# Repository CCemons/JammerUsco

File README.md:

# JammerUsco — Prototipo Inhibidor de Señales en la Banda Libre de 2.4 GHz

**Universidad Surcolombiana (USCO)** — Facultad de Ingeniería — Programa de Ingeniería Electrónica  
**Autores:** Camilo Andrés Castañeda Polo ([@CCemons](https://github.com/CCemons)) · Daniel Camilo Torres Quintana ([@BlackSorix](https://github.com/BlackSorix))  
**Director:** Ing. Martín Diómedes Bravo Obando  

---

## Propósito del Repositorio (Estudio y Replicación Abierta)

Este repositorio reúne **todos los recursos de ingeniería necesarios para estudiar, analizar y replicar íntegramente** el prototipo **JammerUsco**, desarrollado como trabajo de grado para el estudio experimental de técnicas de interferencia intencional (*jamming*) y coexistencia espectral en la banda ISM de **2.4 GHz (2400–2525 MHz)**.

El repositorio está estructurado en **tres bloques fundamentales** para permitir su reproducción completa en laboratorio:

1. **[Código Fuente del Firmware (`src/`, `include/`, `platformio.ini`)](#-1-código-fuente-del-firmware-src-include)**: Firmware en C++ sobre el marco Arduino y el sistema operativo en tiempo real **FreeRTOS** para el SoC **ESP32 (30 pines)**, con ejecución paralela en ambos núcleos, control de doble bus SPI a 16 MHz (`VSPI` y `HSPI`), interfaz gráfica en pantalla OLED `SSD1306` y control remoto por puerto serie (`CLI`).
2. **[Diseño de Circuitos Impresos — PCB (`PCB/`)](#-2-diseño-electrónico-y-fabricación-de-pcb-pcb)**: Proyectos nativos en **KiCad**, librerías propias de símbolos y huellas (*footprints*), archivos estándar de manufactura **Gerber / Excellon Drill** y código G de ruteo mecánico **CNC** tanto para la tarjeta principal (*Mainboard*) como para el módulo de botonera (*Buttons*).
3. **[Modelos Mecánicos 3D (`3D/`)](#-3-modelos-3d-y-chasis-mecánico-3d)**: Archivos CAD universales en formato **STEP (`.step`)** del chasis dividido en dos mitades (listos para laminado e impresión 3D FDM) junto con los modelos tridimensionales de las placas electrónicas ensambladas.

> **Aviso de uso académico:** Este diseño y su código fuente se publican exclusivamente con fines académicos, pedagógicos y de investigación experimental en recintos controlados de laboratorio.

---

## Mapa General del Repositorio

```text
JammerUsco/
├── platformio.ini                  # Configuración de compilación y librerías en PlatformIO
├── README.md                       # Guía general de estudio y replicación del proyecto
│
├── src/                            # [1] CÓDIGO FUENTE DEL FIRMWARE (C++ / FreeRTOS)
│   ├── README.md                   # Documentación de la arquitectura de software
│   ├── main.cpp                    # Orquestación multinúcleo (Core 0: RF / Core 1: UI + CLI)
│   ├── radio_control.cpp           # Control SPI dual (VSPI/HSPI 16 MHz) y algoritmos de barrido
│   ├── display_menu.cpp            # Máquina de estados finitos (FSM) e interfaz OLED SSD1306
│   ├── cli_handler.cpp             # Intérprete de comandos remotos por UART (115200 bps)
│   └── globals.cpp                 # Variables globales volátiles y semáforo mutex (radioMutex)
│
├── include/                        # CABECERAS (.h) DEL FIRMWARE
│   ├── radio_control.h             # Prototipos de inicialización y modos de emisión RF
│   ├── display_menu.h              # Estructuras y prototipos del menú interactivo OLED
│   ├── cli_handler.h               # Declaración del parser de comandos por puerto serie
│   ├── globals.h                   # Definición de pines (GPIO), constantes y estado global
│   └── screensaver_frames.h        # Mapas de bits (PROGMEM) del protector de pantalla OLED
│
├── PCB/                            # [2] DISEÑO DE PCB, GERBERS Y RUTEO CNC
│   ├── README.md                   # Guía de apertura en KiCad y fabricación de las PCBs
│   ├── Kicad_Project/              # Proyectos nativos KiCad + salidas Gerber y Drill
│   │   ├── JammerUsco/             # Proyecto KiCad de la tarjeta principal (Mainboard)
│   │   ├── JammerUsco_Buttons/     # Proyecto KiCad de la tarjeta de pulsadores (Buttons)
│   │   ├── Gerber/                 # Archivos Gerber (.gbr) de ambas tarjetas
│   │   └── Drill/                  # Archivos de perforación Excellon (.drl) PTH y NPTH
│   ├── SYMBOLS_&_FOOTPRINTS/       # Librerías KiCad personalizadas (.kicad_sym / .kicad_mod)
│   └── CNC/Mainboard/              # Archivos G-Code (.nc/.ngc) y mapa de autoleveling (G31)
│
└── 3D/                             # [3] MODELOS CAD 3D (STEP) PARA IMPRESIÓN Y ENSAMBLE
    ├── README.md                   # Guía de impresión 3D y ensamblaje mecánico
    ├── Fusion_3D_Case_Caja_Mitad_Superior_EXPORTADO.step   # Tapa superior del chasis
    ├── Fusion_3D_Case_Caja_Mitad_Inferior_EXPORTADO.step   # Base inferior del chasis
    ├── JammerUsco.step             # Ensamble 3D completo de la PCB principal
    ├── JammerUsco_Buttons.step     # Ensamble 3D completo de la PCB de botonera
    └── Weewooday I2C OLED 0.98” 128x64.step                # Modelo CAD 3D del módulo OLED
```

---

## Guía de Replicación Paso a Paso

### Lista de Materiales (BOM)

| Componente | Cantidad | Especificación Técnica | Función en el Prototipo |
| :--- | :---: | :--- | :--- |
| **ESP32 DevKit V1 (30 pines)** | 1 | Dual-Core Xtensa LX6 a 240 MHz | Unidad central de procesamiento y control SPI/I2C |
| **nRF24L01+PA+LNA (SMA)** | 2 | Banda 2.4 GHz, PA +20 dBm, antena dipolo 2 dBi | Transceptores RF en portadora continua (`VSPI` y `HSPI`) |
| **Módulo Buck LM2596 (HW-411)** | 1 | Entrada 12 V DC → Salida ajustada a **5.0 V DC** | Regulación primaria de alta eficiencia |
| **Módulo LDO AMS1117-3.3V** | 1 | Entrada 5.0 V DC → Salida regulada **3.3 V DC** | Alimentación dedicada y filtrada para la etapa RF |
| **Pantalla OLED 0.96" I2C** | 1 | Controlador `SSD1306`, resolución 128 × 64 px | Interfaz gráfica local de usuario (GUI) |
| **Pulsadores táctiles (12 mm)** | 4 | SPST normalmente abiertos con capuchón | Navegación física (`UP`, `DOWN`, `OK`, `BACK`) |
| **Capacitores de desacoplo** | 2 | Electrolíticos de $10\text{ }\mu\text{F}$ a $100\text{ }\mu\text{F}$ | Filtrado de rizado transitorio en riel de 3.3 V |
| **Fuente de alimentación externa** | 1 | Adaptador 12 V DC / 2 A (conector plug DC) | Suministro energético principal del sistema |

---

### 1. Código Fuente del Firmware (`src/`, `include/`)

El firmware explota la arquitectura de doble núcleo del **ESP32** mediante **FreeRTOS** para garantizar que el refresco de la pantalla OLED por $I^2C$ no introduzca latencias ni tiempos muertos en la conmutación de canales de radiofrecuencia:

- **Núcleo 0 (`jammerTask`):** Ejecuta en un lazo dedicado los algoritmos de barrido espectral sobre los dos módulos `nRF24L01+PA+LNA` a través de los buses independientes `VSPI` y `HSPI` configurados a **16 MHz**. Incluye cuatro modos de operación:
  1. **Modo 1 (`Random`):** Salto pseudoaleatorio continuo sobre los 80 canales ISM ($2400\text{–}2479\text{ MHz}$).
  2. **Modo 2 (`Double Sweep`):** Barrido triangular codireccional sincronizado.
  3. **Modo 3 (`Fixed Channel`):** Portadora continua estacionaria en un canal seleccionable ($0\text{–}125$).
  4. **Modo 4 (`Wi-Fi Sweep`):** Barrido acotado a los 22 MHz de un canal Wi-Fi IEEE 802.11b/g/n seleccionable (canales 1 al 13).
- **Núcleo 1 (`loop()` Arduino):** Gestiona la lectura con antirrebote de los 4 pulsadores físicos, el renderizado de la máquina de estados en la pantalla OLED `SSD1306` y el intérprete de comandos por puerto serie (`115200 bps`).
- **Sincronización (`radioMutex`):** Un semáforo tipo *mutex* de FreeRTOS protege todas las transacciones sobre los buses SPI para evitar colisiones entre el lazo de barrido del Núcleo 0 y los cambios de configuración solicitados desde el Núcleo 1.

#### Mapa de Conexiones (Pinout ESP32 de 30 Pines)

| Subsistema | Señal | Pin ESP32 | Descripción |
| :--- | :---: | :---: | :--- |
| **Radio 1 (`VSPI`)** | `CE` / `CSN` | `GPIO 22` / `GPIO 21` | Habilitación de chip y selección de esclavo SPI 1 |
| **Radio 1 (`VSPI`)** | `SCK` / `MOSI` / `MISO` | `GPIO 18` / `GPIO 23` / `GPIO 19` | Reloj y líneas de datos del bus `VSPI` (16 MHz) |
| **Radio 2 (`HSPI`)** | `CE` / `CSN` | `GPIO 16` / `GPIO 15` | Habilitación de chip y selección de esclavo SPI 2 |
| **Radio 2 (`HSPI`)** | `SCK` / `MOSI` / `MISO` | `GPIO 14` / `GPIO 13` / `GPIO 12` | Reloj y líneas de datos del bus `HSPI` (16 MHz) |
| **Pantalla OLED (`I2C`)** | `SDA` / `SCL` | `GPIO 27` / `GPIO 26` | Bus $I^2C$ por software hacia pantalla `SSD1306` |
| **Botonera (`INPUT_PULLUP`)** | `UP` / `DOWN` / `OK` / `BACK` | `GPIO 33` / `GPIO 25` / `GPIO 32` / `GPIO 4` | Pulsadores activos en nivel bajo (`LOW`) |

#### Compilación y Carga con PlatformIO

1. Instalar [Visual Studio Code](https://code.visualstudio.com/) con la extensión **PlatformIO IDE**.
2. Clonar este repositorio y abrir la carpeta raíz en PlatformIO (`platformio.ini` descargará automáticamente las librerías `RF24 @ ^1.4.8`, `Adafruit SSD1306 @ ^2.5.7`, `Adafruit GFX @ ^1.11.9` y `ezButton @ ^1.0.4`).
3. Compilar y cargar el firmware al ESP32:
   ```bash
   pio run --target upload
   pio device monitor -b 115200
   ```

#### Comandos por Puerto Serie (`UART 115200 bps`)

| Comando | Función |
| :---: | :--- |
| `'s'` / `'p'` | Iniciar (`Start`) / Detener (`Stop`) la emisión de portadora continua RF |
| `'o'` / `'t'` / `'w'` | Seleccionar modo `Random` / `Double Sweep` / `Wi-Fi` |
| `'m'` / `'l'` / `'h'` / `'x'` | Ajustar potencia PA: `MIN (2 dBm)` / `LOW (8 dBm)` / `HIGH (14 dBm)` / `MAX (20 dBm)` |
| `'k'` / `'1'` / `'2'` | Ajustar tasa de datos RF (ensanchamiento): `250 kbps` / `1 Mbps` / `2 Mbps` |
| `'u'`/`'U'`, `'v'`/`'V'`, `'e'`, `'b'` | Emular pulsaciones cortas/largas de los botones (`UP`, `DOWN`, `OK`, `BACK`) |
| `'d'` | Imprimir diagnóstico de comunicación SPI y estado de registros `nRF24L01+` |

---

### 2. Diseño Electrónico y Fabricación de PCB (`PCB/`)

El diseño electrónico se divide en dos tarjetas independientes de una sola cara (*single-layer* en la capa `B.Cu`) optimizadas tanto para manufactura industrial como para fresado químico o mecánico CNC:

1. **Tarjeta Principal (`PCB/Kicad_Project/JammerUsco/`):** Integra el ESP32, los dos zócalos para los transceptores `nRF24L01+PA+LNA` con geometría de pistas simétrica, la cascada de regulación `LM2596` (12 V → 5 V) + `AMS1117-3.3V` (5 V → 3.3 V) y los conectores hacia la pantalla OLED y la botonera.
2. **Tarjeta de Botonera (`PCB/Kicad_Project/JammerUsco_Buttons/`):** Aloja los 4 pulsadores táctiles de 12 mm que se fijan en el panel frontal superior del chasis.

- **Para manufactura con archivos Gerber:** Utilizar los archivos listos en `PCB/Kicad_Project/Gerber/` y `PCB/Kicad_Project/Drill/`.
- **Para fabricación en fresadora CNC:** Utilizar los archivos de código G en `PCB/CNC/Mainboard/` (`JammerUsco-B_Cu_adjusted.ngc` para aislamiento de pistas y `JammerUsco-PTH.nc` para perforación).

📄 *Consulte más detalles en [`PCB/README.md`](PCB/README.md).*

---

### 3. Modelos 3D y Chasis Mecánico (`3D/`)

La carpeta `3D/` contiene todos los sólidos geométricos en estándar **ISO 10303-21 (`.step`)**, compatibles con cualquier software CAD (*Autodesk Fusion 360*, *SolidWorks*, *FreeCAD*) y laminadores de impresión 3D (*PrusaSlicer*, *UltiMaker Cura*, *Bambu Studio*, *OrcaSlicer*):

- **`Fusion_3D_Case_Caja_Mitad_Superior_EXPORTADO.step`:** Tapa superior del gabinete con vano biselado para la pantalla OLED de 0.96", cuatro guías cilíndricas para los pulsadores de 12 mm y rejillas laterales de ventilación por convección.
- **`Fusion_3D_Case_Caja_Mitad_Inferior_EXPORTADO.step`:** Base inferior con torretas de fijación para la PCB principal, aberturas traseras para los conectores coaxiales SMA de ambos radios `nRF24L01+PA+LNA` y acceso lateral para alimentación DC y puerto micro-USB.
- **`JammerUsco.step` y `JammerUsco_Buttons.step`:** Ensambles tridimensionales completos de las tarjetas electrónicas exportados desde KiCad para verificación de tolerancias mecánicas.

📄 *Consulte los parámetros recomendados de impresión 3D en [`3D/README.md`](3D/README.md).*

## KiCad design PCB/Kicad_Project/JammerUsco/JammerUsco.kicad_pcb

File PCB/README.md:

# Diseño Electrónico y Fabricación de PCB (`PCB/`)

Esta carpeta contiene todos los archivos de diseño asistido por computador (ECAD) y manufactura asistida por computador (CAM) correspondientes a las dos tarjetas de circuito impreso del prototipo **JammerUsco**:

1. **Tarjeta Principal (`Mainboard` — `JammerUsco`):** Interconecta el módulo **ESP32 (30 pines)**, los dos transceptores **nRF24L01+PA+LNA** sobre los buses dedicados `VSPI` y `HSPI`, la etapa de conversión DC-DC **LM2596 (5.0 V)**, el regulador lineal **AMS1117-3.3V** dedicado a la etapa de radiofrecuencia, y las cabeceras de conexión para la pantalla OLED $I^2C$ y la botonera.
2. **Tarjeta de Botonera (`Buttons` — `JammerUsco_Buttons`):** Placa auxiliar para los 4 pulsadores táctiles de $12\text{ mm} \times 12\text{ mm}$ (`UP`, `DOWN`, `OK`, `BACK`) con retorno común a tierra (`GND`).

---

## Estructura de Directorios

```text
PCB/
├── Kicad_Project/
│   ├── JammerUsco/                 # Proyecto KiCad nativo de la PCB principal (Mainboard)
│   │   ├── JammerUsco.kicad_pro    # Archivo de proyecto KiCad
│   │   ├── JammerUsco.kicad_sch    # Esquemático electrónico completo
│   │   └── JammerUsco.kicad_pcb    # Ruteo de la PCB (capa B.Cu + plano de masa GND)
│   ├── JammerUsco_Buttons/         # Proyecto KiCad nativo del módulo de 4 pulsadores
│   ├── Gerber/
│   │   ├── Mainboard/              # Archivos Gerber (B_Cu, Edge_Cuts, gbrjob) de la placa principal
│   │   └── Buttons/                # Archivos Gerber (B_Cu, Edge_Cuts, gbrjob) de la botonera
│   └── Drill/
│       ├── Mainboard/              # Perforaciones Excellon (.drl PTH y NPTH) de la placa principal
│       └── Buttons/                # Perforaciones Excellon (.drl PTH y NPTH) de la botonera
│
├── SYMBOLS_&_FOOTPRINTS/           # Librerías personalizadas KiCad creadas para el proyecto
│   ├── AMS1117_3.3V/               # Símbolo (.kicad_sym) y huella (.kicad_mod) del LDO AMS1117
│   ├── ESP32/                      # Símbolo y huella del DevKit ESP32 de 30 pines
│   ├── LM2596_BUCK_5V/             # Símbolo y huella del módulo convertidor Buck LM2596
│   └── NRF24L01/                   # Símbolo y huella del transceptor nRF24L01+PA+LNA
│
└── CNC/Mainboard/                  # Archivos G-Code para fresado mecánico en CNC 6040
    ├── JammerUsco-B_Cu.gbr_ncc_cnc.nc      # Trayectoria base de aislamiento de pistas (B.Cu)
    ├── JammerUsco-B_Cu_probe_only.ngc      # Rutina de sondeo superficial (G31) en malla 6×8
    ├── map.txt                             # Mapa topográfico real de cotas Z medidas en el laminado FR-4
    ├── JammerUsco-B_Cu_adjusted.ngc        # Código G final compensado en Z para ruteo de cobre
    └── JammerUsco-PTH.nc                   # Código G de taladrado de agujeros pasantes (PTH)
```

---

## Cómo Replicar las Tarjetas PCB

### Opción A: Fabricación Industrial o Química con Archivos Gerber
Si desea enviar las placas a un fabricante externo (JLCPCB, PCBWay, ALLPCB) o realizar revelado fotográfico/transferencia térmica:
1. Comprima en un archivo `.zip` el contenido de `Kicad_Project/Gerber/Mainboard/` junto con `Kicad_Project/Drill/Mainboard/` para la placa principal.
2. Comprima en otro `.zip` el contenido de `Kicad_Project/Gerber/Buttons/` junto con `Kicad_Project/Drill/Buttons/` para la botonera.
3. Especifique laminado **FR-4**, espesor **1.6 mm**, 1 capa de cobre (`Bottom Layer / B.Cu`) y peso de cobre de **1 oz (35 µm)**.

### Opción B: Fresado Mecánico en Ruteadora CNC
Si dispone de una fresadora CNC con control **Mach3 / GRBL**:
1. Sujete una placa virgen de baquelita o **FR-4 de una cara** sobre la mesa de sacrificio.
2. Ejecute el sondeo de nivelación superficial (`G31`) o utilice directamente `CNC/Mainboard/JammerUsco-B_Cu_adjusted.ngc` con una fresa tipo *V-bit* de grabado de **0.2 mm a 0.6 mm**.
3. Ejecute el taladrado de agujeros pasantes con `CNC/Mainboard/JammerUsco-PTH.nc` usando broca de carburo de tungsteno de **0.8 mm – 1.0 mm**.

### Cómo Abrir y Modificar el Proyecto en KiCad
1. Abra **KiCad 8.0 / 9.0+** y cargue `Kicad_Project/JammerUsco/JammerUsco.kicad_pro`.
2. Si desea editar componentes, vincule en *Preferencias → Configurar bibliotecas de símbolos / huellas* las 4 carpetas incluidas en `SYMBOLS_&_FOOTPRINTS/`.

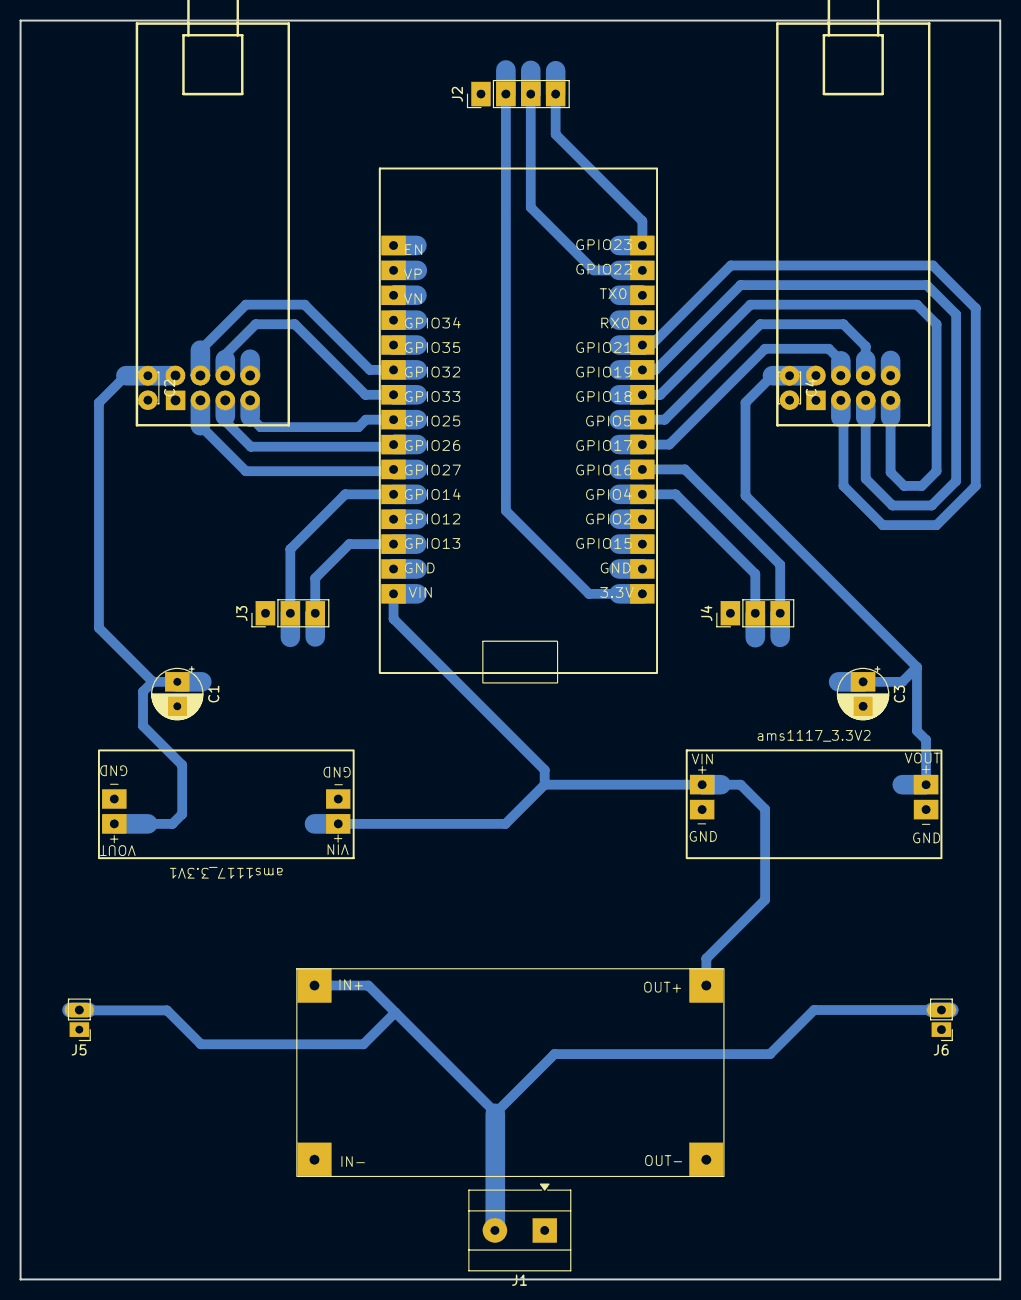
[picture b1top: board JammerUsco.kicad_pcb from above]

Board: 2 copper layers, 100.0 x 128.5 mm, 16 parts (0 on the bottom side), 22 nets.

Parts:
C1, C3: C_10uF; CP_Radial_D5.0mm_P2.50mm
C2, C4: C_0.1uF; C_Disc_D3.0mm_W2.0mm_P2.50mm
ESP32_30pin1: ESP32_30pin
J1: 12V; TerminalBlock_MetzConnect_Type101_RT01602HBWC_1x02_P5.08mm_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
J2: Display; PinHeader_1x04_P2.54mm_Vertical
J3: Up_down_btts; PinHeader_1x03_P2.54mm_Vertical
J4: Ok_back_btts; PinHeader_1x03_P2.54mm_Vertical
J5: Amp1; PinHeader_1x02_P2.00mm_Vertical
J6: Amp2; PinHeader_1x02_P2.00mm_Vertical
LM2596_BUCK_MODULE_5V1: LM2596_BUCK_MODULE_5V
NRF24L01+PA+LNA1, NRF24L01+PA+LNA2: NRF24L01_PA_LNA
ams1117_3.3V1, ams1117_3.3V2: ams1117_module_3.3V

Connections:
3.3V R1: C1.1, C2.1, NRF24L01+PA+LNA1.2 (VCC), ams1117_3.3V1.3 (Vout)
3.3V R2: C3.1, C4.1, NRF24L01+PA+LNA2.2 (VCC), ams1117_3.3V2.3 (Vout)
5V: ESP32_30pin1.1 (VIN), LM2596_BUCK_MODULE_5V1.3 (OUT+), ams1117_3.3V1.1 (Vin), ams1117_3.3V2.1 (Vin)
12V: J1.2, J5.2, J6.2, LM2596_BUCK_MODULE_5V1.1 (IN+)
Back btt: ESP32_30pin1.21 (GPIO16), J4.3
CE1: ESP32_30pin1.6 (GPIO27), NRF24L01+PA+LNA1.3 (CE)
CE2: ESP32_30pin1.26 (GPIO21), NRF24L01+PA+LNA2.3 (CE)
CSN1: ESP32_30pin1.10 (GPIO32), NRF24L01+PA+LNA1.4 (CSN)
CSN2: ESP32_30pin1.22 (GPIO17), NRF24L01+PA+LNA2.4 (CSN)
Down btt: ESP32_30pin1.3 (GPIO13), J3.3
ESP32 3.3V: ESP32_30pin1.16 (3.3V), J2.2
GND: C1.2, C2.2, C3.2, C4.2, ESP32_30pin1.2 (GND), ESP32_30pin1.17 (GND), J1.1, J2.1, J3.1, J4.1, J5.1, J6.1, LM2596_BUCK_MODULE_5V1.2 (IN-), LM2596_BUCK_MODULE_5V1.4 (OUT-), NRF24L01+PA+LNA1.1 (GND), NRF24L01+PA+LNA2.1 (GND), ams1117_3.3V1.2 (GND), ams1117_3.3V1.4 (GND), ams1117_3.3V2.2 (GND), ams1117_3.3V2.4 (GND)
MISO1: ESP32_30pin1.8 (GPIO25), NRF24L01+PA+LNA1.7 (MISO)
MISO2: ESP32_30pin1.24 (GPIO18), NRF24L01+PA+LNA2.7 (MISO)
MOSI1: ESP32_30pin1.9 (GPIO33), NRF24L01+PA+LNA1.6 (MOSI)
MOSI2: ESP32_30pin1.23 (GPIO5), NRF24L01+PA+LNA2.6 (MOSI)
Ok btt: ESP32_30pin1.20 (GPIO4), J4.2
SCK1: ESP32_30pin1.7 (GPIO26), NRF24L01+PA+LNA1.5 (SCK)
SCK2: ESP32_30pin1.25 (GPIO19), NRF24L01+PA+LNA2.5 (SCK)
SCL: ESP32_30pin1.29 (GPIO22), J2.3
SDA: ESP32_30pin1.30 (GPIO23), J2.4
Up btt: ESP32_30pin1.5 (GPIO14), J3.2
